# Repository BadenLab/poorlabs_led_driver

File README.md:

# Poorlabs stimulus generator
A custom driver for Chrolis LED system from ThorLabs

This repository contains all the documentation needed to build a custom driver for a [Chrolis LED system from Thorlabs](https://www.thorlabs.com/newgrouppage9.cfm?objectgroup_id=13597).

Features:
- Synchronisation with 2 photon microscope blanking signal (or any other synchronisation TTL pulse)
  - Synchronisation done via hardware, dispensing the need to include complicated logic on the microcontroller
- Based on ESP32 (uses [BeeHive](https://github.com/BeeHive-org/BeeHive) main breakout board)
- Set of stimuli provided. Based on [Led Zappelin's code](https://github.com/BadenLab/LED-Zappelin)

Skills required:
- Coding (Arduino IDE / Micropython)
- Soldering
- Using a drill, screwdriver

Links/tutorials used:
- [getting started with ESP 32 and micropython](https://docs.micropython.org/en/latest/esp32/tutorial/intro.html)
- [controlling an ESP with micropython via a Jupyter notebook](https://towardsdatascience.com/micropython-on-esp-using-jupyter-6f366ff5ed9) 
- datasheets:
  - [Chips performing logical AND on the signals to control each LED and the blanking signal](https://www.mouser.co.uk/datasheet/2/308/74LS08-1190273.pdf)
  - [Chip inverting the blanking signal (logical NOT)](https://www.mouser.co.uk/datasheet/2/308/1/MC74HC14A_D-2315678.pdf)

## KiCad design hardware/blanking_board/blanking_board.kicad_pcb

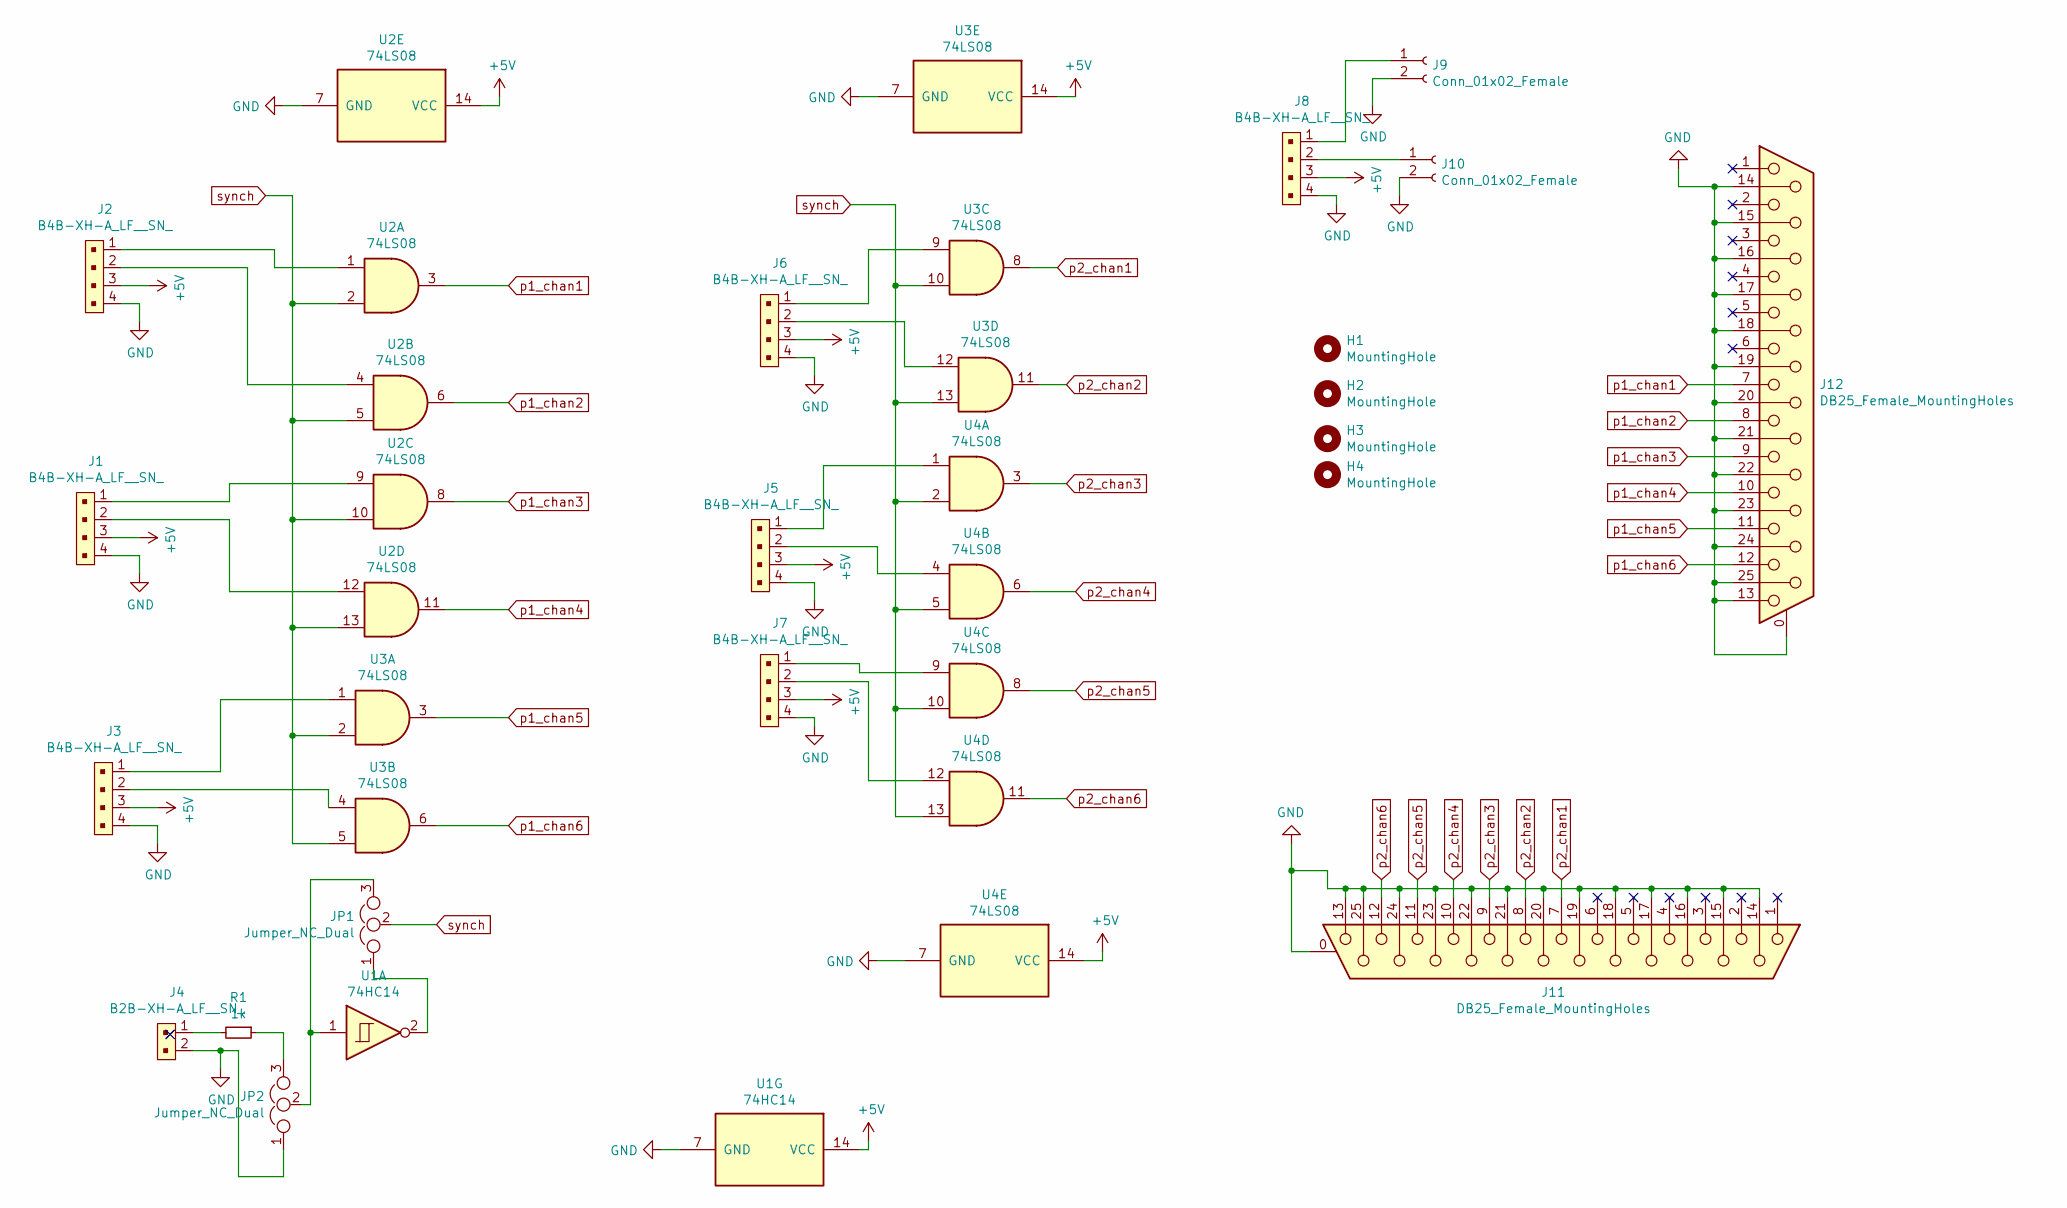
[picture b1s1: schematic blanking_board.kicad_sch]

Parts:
H1, H2, H3, H4: MountingHole; MountingHole_3.2mm_M3_ISO7380
J1, J2, J3, J5, J6, J7, J8: B4B-XH-A_LF__SN_; JST_XH_B4B-XH-A_1x04_P2.50mm_Vertical; MPN B4B-XH-A(LF)(SN); Digi-Key_PN 455-2249-ND
J4: B2B-XH-A_LF__SN_; JST_XH_B2B-XH-A_1x02_P2.50mm_Vertical; MPN B2B-XH-A(LF)(SN); Digi-Key_PN 455-2247-ND
J9, J10: Conn_01x02_Female; JST_XH_B2B-XH-A_1x02_P2.50mm_Vertical
J11, J12: DB25_Female_MountingHoles; PinHeader_2x13_P2.54mm_Vertical
JP1, JP2: Jumper_NC_Dual; PinHeader_1x03_P2.54mm_Vertical
R1: 1k; R_Axial_DIN0411_L9.9mm_D3.6mm_P15.24mm_Horizontal
U1: 74HC14; DIP-14_W7.62mm_LongPads
U2, U3, U4: 74LS08; DIP-14_W7.62mm_LongPads

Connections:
+5V: J1.3, J2.3, J3.3, J5.3, J6.3, J7.3, J8.3, U1.14 (VCC), U2.14 (VCC), U3.14 (VCC), U4.14 (VCC)
GND: J1.4, J2.4, J3.4, J4.2, J5.4, J6.4, J7.4, J8.4, J9.2, J10.2, J11.0 (PAD), J11.13, J11.14, J11.15, J11.16, J11.17, J11.18, J11.19, J11.20, J11.21, J11.22, J11.23, J11.24, J11.25, J12.0 (PAD), J12.13, J12.14, J12.15, J12.16, J12.17, J12.18, J12.19, J12.20, J12.21, J12.22, J12.23, J12.24, J12.25, JP2.1, U1.7 (GND), U2.7 (GND), U3.7 (GND), U4.7 (GND)
unnamed: J1.1, U2.9
unnamed: J1.2, U2.12
unnamed: J2.1, U2.1
unnamed: J2.2, U2.4
unnamed: J3.1, U3.1
unnamed: J3.2, U3.4
unnamed: J4.1, R1.2
unnamed: J5.1, U4.1
unnamed: J5.2, U4.4
unnamed: J6.1, U3.9
unnamed: J6.2, U3.12
unnamed: J7.1, U4.9
unnamed: J7.2, U4.12
unnamed: J8.1, J9.1
unnamed: J8.2, J10.1
unnamed: JP1.1, U1.2
unnamed: JP1.3, JP2.2, U1.1
unnamed: JP2.3, R1.1
p1_chan1: J12.7, U2.3
p1_chan2: J12.8, U2.6
p1_chan3: J12.9, U2.8
p1_chan4: J12.10, U2.11
p1_chan5: J12.11, U3.3
p1_chan6: J12.12, U3.6
p2_chan1: J11.7, U3.8
p2_chan2: J11.8, U3.11
p2_chan3: J11.9, U4.3
p2_chan4: J11.10, U4.6
p2_chan5: J11.11, U4.8
p2_chan6: J11.12, U4.11
synch: JP1.2, U2.2, U2.5, U2.10, U2.13, U3.2, U3.5, U3.10, U3.13, U4.2, U4.5, U4.10, U4.13

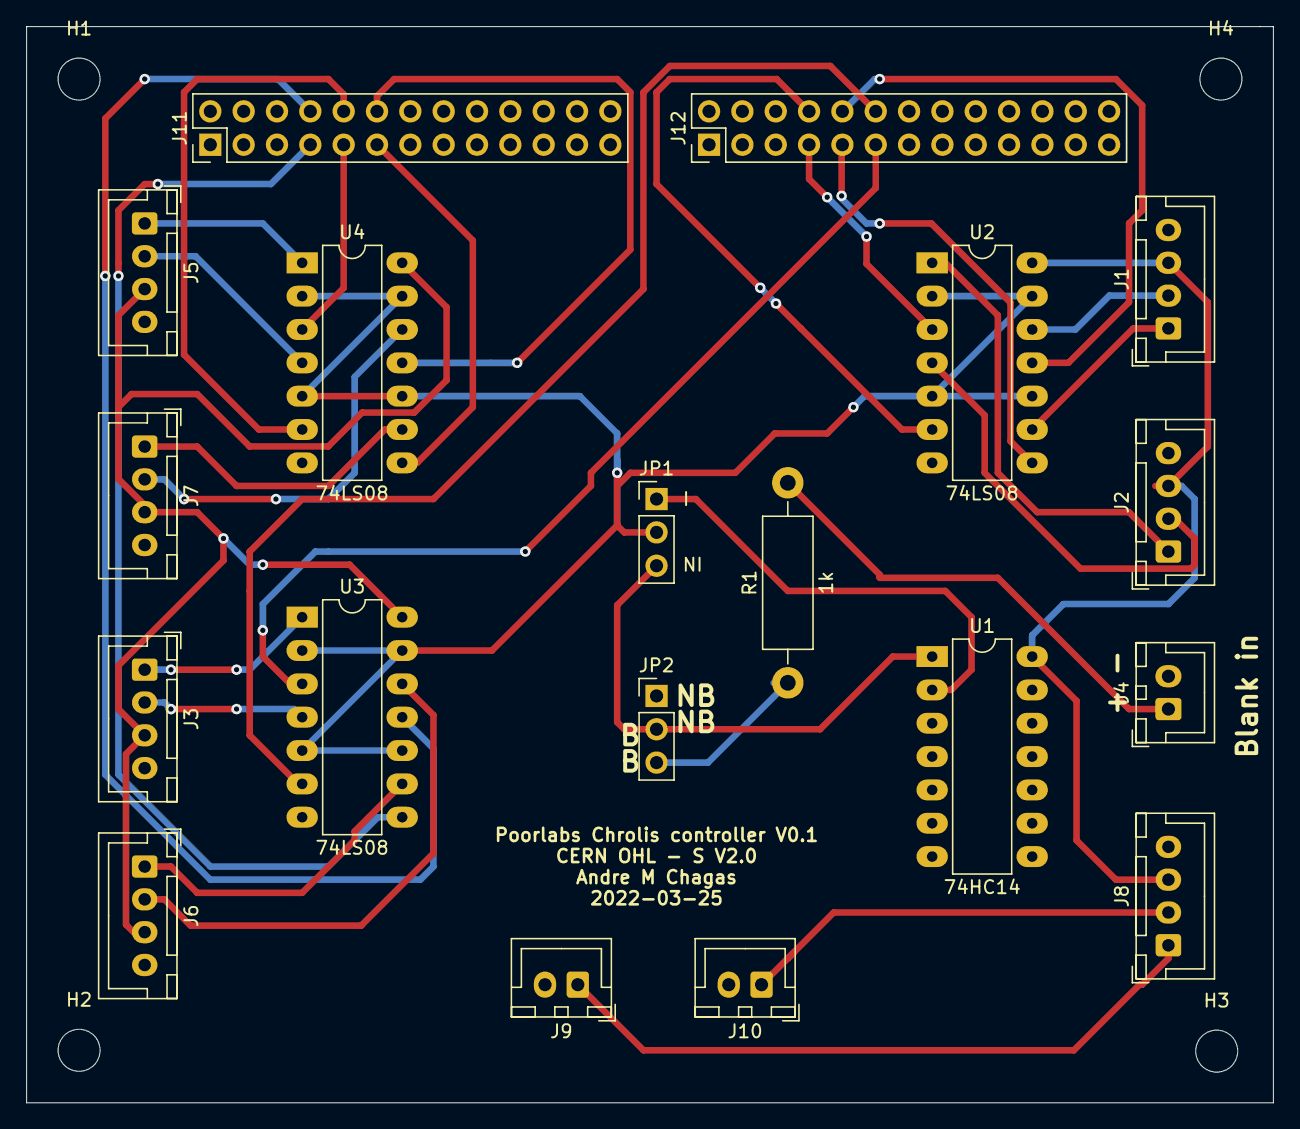
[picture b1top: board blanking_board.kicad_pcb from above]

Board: 2 copper layers, 95.0 x 82.0 mm, 23 parts (0 on the bottom side), 33 nets.

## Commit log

2021-11-03 Create Links
2021-11-18 organise repo and work on electronics schematic
2021-11-18 schematic update
2021-12-06 Create rig_tester.ino
    bit of code to cycle through leds and sync out signal
2021-12-09 first implementation with jupyter notebook
2021-12-13 implemented PWM with RMT system and added first example
2021-12-13 remove commented function
2021-12-16 organise repo and update micropython code
2021-12-16 notebook cleanup
2021-12-16 clean repo and update micropython code
2022-01-13 update on juptyer notebook
2022-03-24 update board
2022-03-25 first version of PCB
2022-07-26 update pcb with jumper for no blanking
2022-07-30 more details on board
2022-07-30 update training board design
2022-08-01 update miropython firmware
2022-10-21 update board details

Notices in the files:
hardware/blanking_board/blanking_board.kicad_pcb:
CERN OHL - S V2.0
